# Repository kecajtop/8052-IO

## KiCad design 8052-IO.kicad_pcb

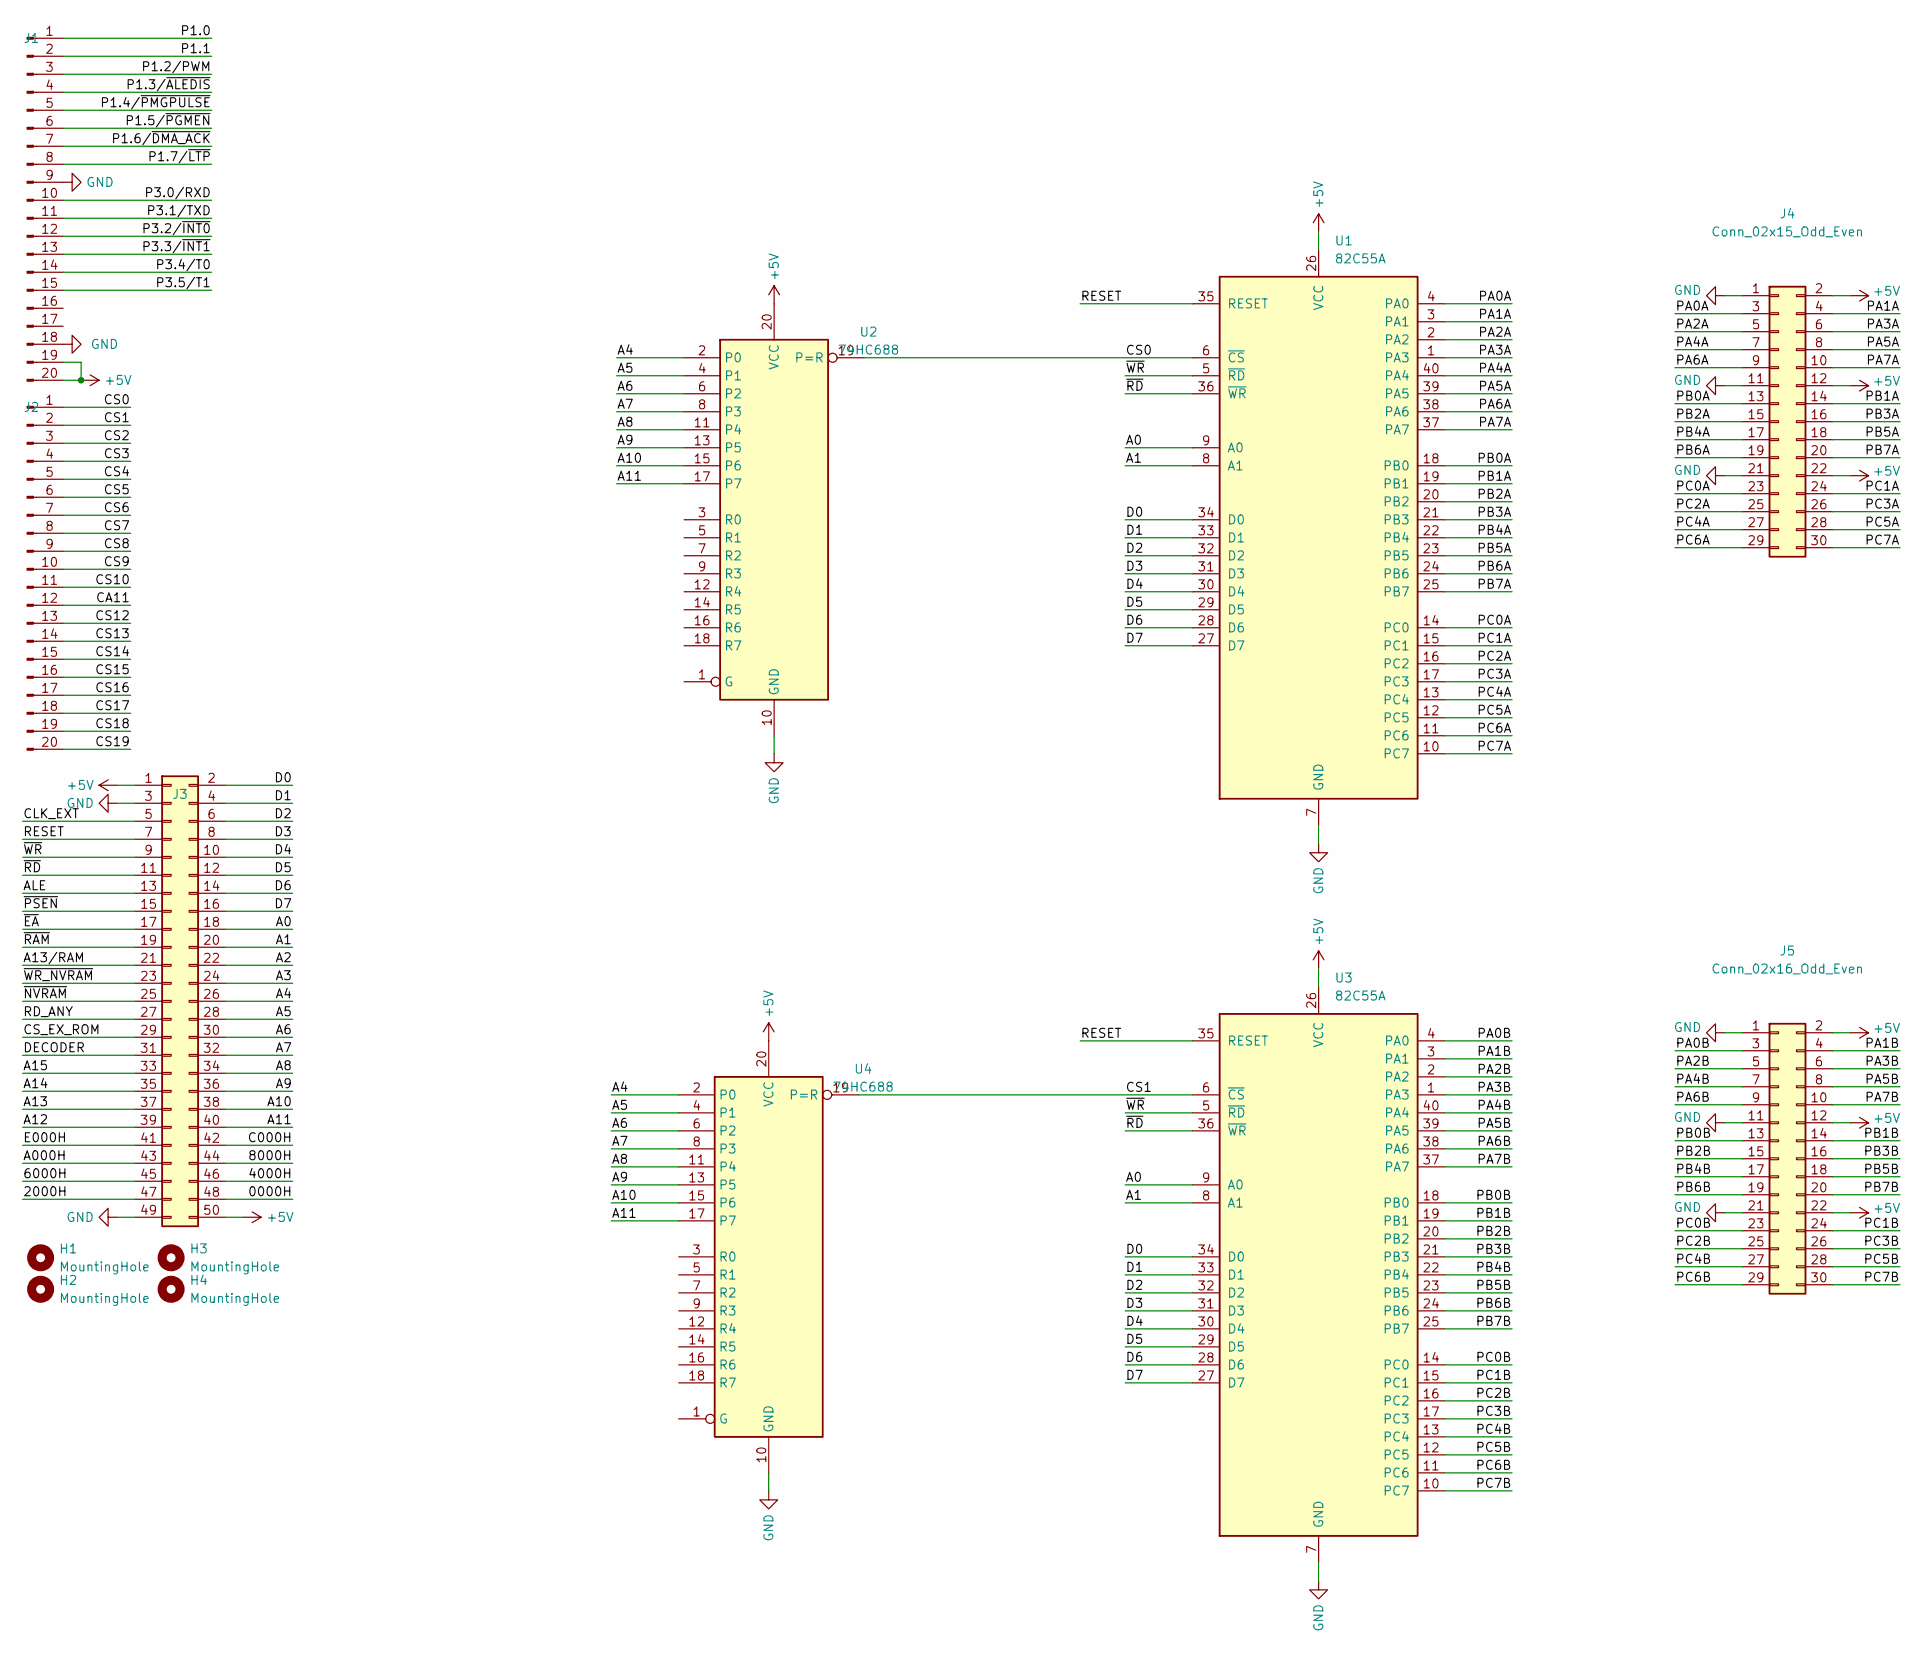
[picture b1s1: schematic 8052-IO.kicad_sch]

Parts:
H1, H2, H3, H4: MountingHole; MountingHole_3.2mm_M3
J1, J2: Conn_01x20_Pin; PinHeader_1x20_P2.54mm_Vertical
J3: Conn_02x25_Odd_Even; PinHeader_2x25_P2.54mm_Vertical
J4: Conn_02x15_Odd_Even; PinHeader_2x15_P2.54mm_Horizontal
J5: Conn_02x16_Odd_Even; PinHeader_2x15_P2.54mm_Horizontal
U1, U3: 82C55A; DIP-40_W15.24mm
U2, U4: 74HC688; SOIC-20W_7.5x12.8mm_P1.27mm

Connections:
+5V: J1.19, J1.20, J3.1, J3.50, J4.2, J4.12, J4.22, J5.2, J5.12, J5.22, U1.26 (VCC), U2.20 (VCC), U3.26 (VCC), U4.20 (VCC)
/0000H: J3.48
/2000H: J3.47
/4000H: J3.46
/6000H: J3.45
/8000H: J3.44
/A0: J3.18, U1.9 (A0), U3.9 (A0)
/A000H: J3.43
/A1: J3.20, U1.8 (A1), U3.8 (A1)
/A2: J3.22
/A3: J3.24
/A4: J3.26, U2.2 (P0), U4.2 (P0)
/A5: J3.28, U2.4 (P1), U4.4 (P1)
/A6: J3.30, U2.6 (P2), U4.6 (P2)
/A7: J3.32, U2.8 (P3), U4.8 (P3)
/A8: J3.34, U2.11 (P4), U4.11 (P4)
/A9: J3.36, U2.13 (P5), U4.13 (P5)
/A10: J3.38, U2.15 (P6), U4.15 (P6)
/A11: J3.40, U2.17 (P7), U4.17 (P7)
/A12: J3.39
/A13: J3.37
/A13/RAM: J3.21
/A14: J3.35
/A15: J3.33
/ALE: J3.13
/C000H: J3.42
/CA11: J2.12
/CLK_EXT: J3.5
/CS0: J2.1, U1.6 (~CS), U2.19 (P=R)
/CS1: J2.2, U3.6 (~CS), U4.19 (P=R)
/CS2: J2.3
/CS3: J2.4
/CS4: J2.5
/CS5: J2.6
/CS6: J2.7
/CS7: J2.8
/CS8: J2.9
/CS9: J2.10
/CS10: J2.11
/CS12: J2.13
/CS13: J2.14
/CS14: J2.15
/CS15: J2.16
/CS16: J2.17
/CS17: J2.18
/CS18: J2.19
/CS19: J2.20
/CS_EX_ROM: J3.29
/D0: J3.2, U1.34 (D0), U3.34 (D0)
/D1: J3.4, U1.33 (D1), U3.33 (D1)
/D2: J3.6, U1.32 (D2), U3.32 (D2)
/D3: J3.8, U1.31 (D3), U3.31 (D3)
/D4: J3.10, U1.30 (D4), U3.30 (D4)
/D5: J3.12, U1.29 (D5), U3.29 (D5)
/D6: J3.14, U1.28 (D6), U3.28 (D6)
/D7: J3.16, U1.27 (D7), U3.27 (D7)
/DECODER: J3.31
/E000H: J3.41
/P1.0: J1.1
/P1.1: J1.2
/P1.2/PWM: J1.3
/P1.3/~ALEDIS: J1.4
/P1.4/~PMGPULSE: J1.5
/P1.5/~PGMEN: J1.6
/P1.6/~DMA_ACK: J1.7
/P1.7/~LTP: J1.8
/P3.0/RXD: J1.10
/P3.1/TXD: J1.11
/P3.2/~INT0: J1.12
/P3.3/~INT1: J1.13
/P3.4/T0: J1.14
/P3.5/T1: J1.15
/PA0A: J4.3, U1.4 (PA0)
/PA0B: J5.3, U3.4 (PA0)
/PA1A: J4.4, U1.3 (PA1)
/PA1B: J5.4, U3.3 (PA1)
/PA2A: J4.5, U1.2 (PA2)
/PA2B: J5.5, U3.2 (PA2)
/PA3A: J4.6, U1.1 (PA3)
/PA3B: J5.6, U3.1 (PA3)
/PA4A: J4.7, U1.40 (PA4)
/PA4B: J5.7, U3.40 (PA4)
/PA5A: J4.8, U1.39 (PA5)
/PA5B: J5.8, U3.39 (PA5)
/PA6A: J4.9, U1.38 (PA6)
/PA6B: J5.9, U3.38 (PA6)
/PA7A: J4.10, U1.37 (PA7)
/PA7B: J5.10, U3.37 (PA7)
/PB0A: J4.13, U1.18 (PB0)
/PB0B: J5.13, U3.18 (PB0)
/PB1A: J4.14, U1.19 (PB1)
/PB1B: J5.14, U3.19 (PB1)
/PB2A: J4.15, U1.20 (PB2)
/PB2B: J5.15, U3.20 (PB2)
/PB3A: J4.16, U1.21 (PB3)
/PB3B: J5.16, U3.21 (PB3)
/PB4A: J4.17, U1.22 (PB4)
/PB4B: J5.17, U3.22 (PB4)
/PB5A: J4.18, U1.23 (PB5)
/PB5B: J5.18, U3.23 (PB5)
/PB6A: J4.19, U1.24 (PB6)
/PB6B: J5.19, U3.24 (PB6)
/PB7A: J4.20, U1.25 (PB7)
/PB7B: J5.20, U3.25 (PB7)
/PC0A: J4.23, U1.14 (PC0)
/PC0B: J5.23, U3.14 (PC0)
/PC1A: J4.24, U1.15 (PC1)
/PC1B: J5.24, U3.15 (PC1)
/PC2A: J4.25, U1.16 (PC2)
/PC2B: J5.25, U3.16 (PC2)
/PC3A: J4.26, U1.17 (PC3)
/PC3B: J5.26, U3.17 (PC3)
/PC4A: J4.27, U1.13 (PC4)
/PC4B: J5.27, U3.13 (PC4)
/PC5A: J4.28, U1.12 (PC5)
/PC5B: J5.28, U3.12 (PC5)
/PC6A: J4.29, U1.11 (PC6)
/PC6B: J5.29, U3.11 (PC6)
/PC7A: J4.30, U1.10 (PC7)
/PC7B: J5.30, U3.10 (PC7)
/RD_ANY: J3.27
/RESET: J3.7, U1.35 (RESET), U3.35 (RESET)
/~EA: J3.17
/~NVRAM: J3.25
/~PSEN: J3.15
/~RAM: J3.19
/~RD: J3.11, U1.36 (~WR), U3.36 (~WR)
/~WR_NVRAM: J3.23
/~WR: J3.9, U1.5 (~RD), U3.5 (~RD)
GND: J1.9, J1.18, J3.3, J3.49, J4.1, J4.11, J4.21, J5.1, J5.11, J5.21, U1.7 (GND), U2.10 (GND), U3.7 (GND), U4.10 (GND)

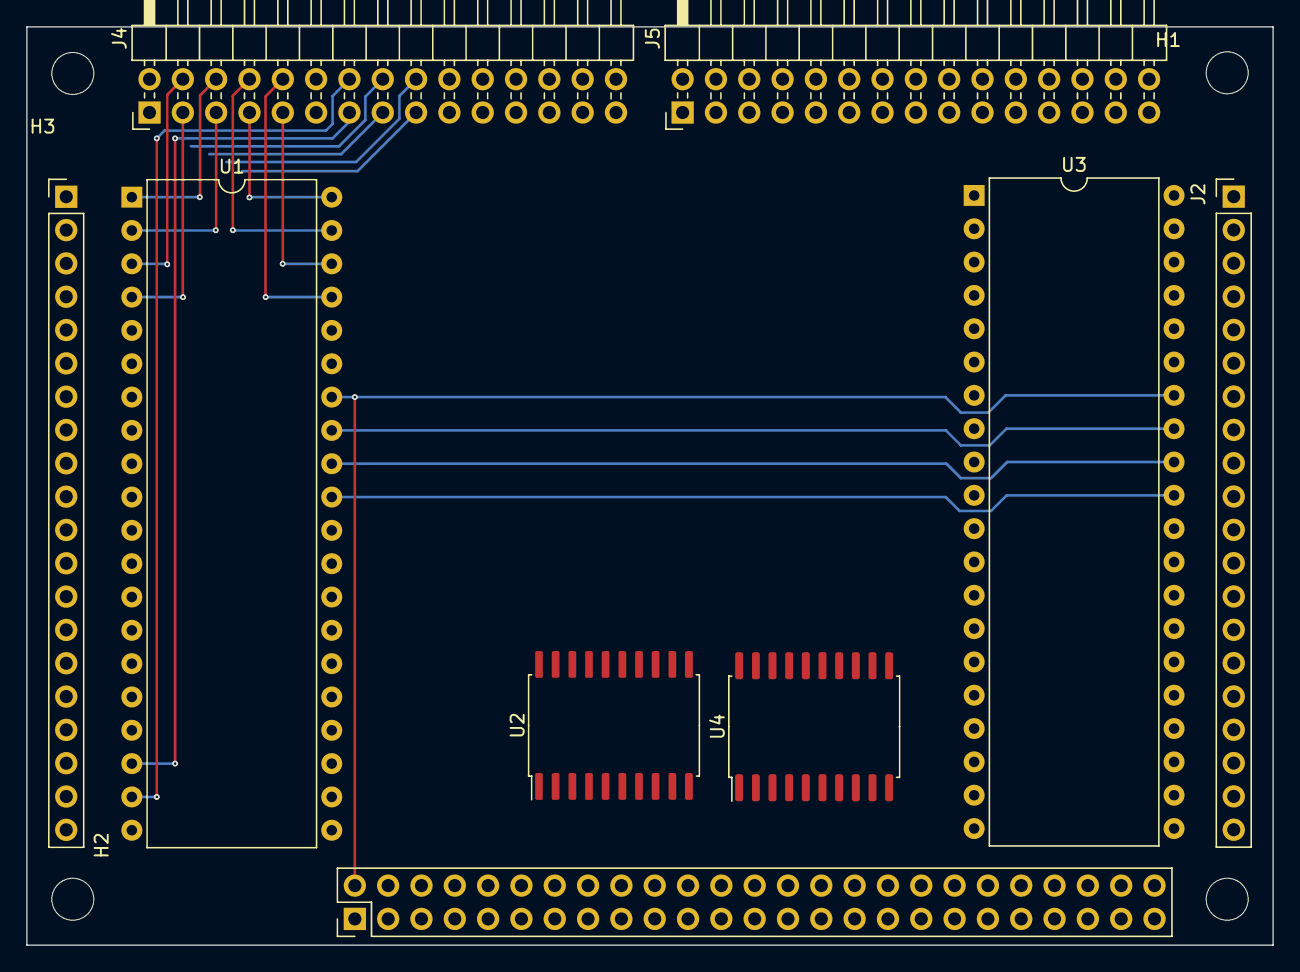
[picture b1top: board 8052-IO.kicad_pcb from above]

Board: 4 copper layers, 95.0 x 70.0 mm, 13 parts (0 on the bottom side), 73 nets.
